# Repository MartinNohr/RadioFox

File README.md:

# RadioFox
Ham Radio Fox Software
This is the code for a TTGO T-Display running an SA818V radio. It is used for fox/bunny hunting.
This code requires the phoneDTMF library from here:
https://github.com/Adrianotiger/phoneDTMF
Install as documents/arduino/libraries/phoneDTMF

7/1/2026 The code has been changed to use VS Code with the pio extension loaded. Load the dtmf file into the VS Code lib folder.
The code also now uses espressif version 3.x instead of 2.x. They had introduced a number of breaking changes in version 3.x that resulted in numerous code changes.

7/28/2026 I went back to core 2.0.17. The 3.x one rebooted constantly. I'll spend some time later figureing out why.

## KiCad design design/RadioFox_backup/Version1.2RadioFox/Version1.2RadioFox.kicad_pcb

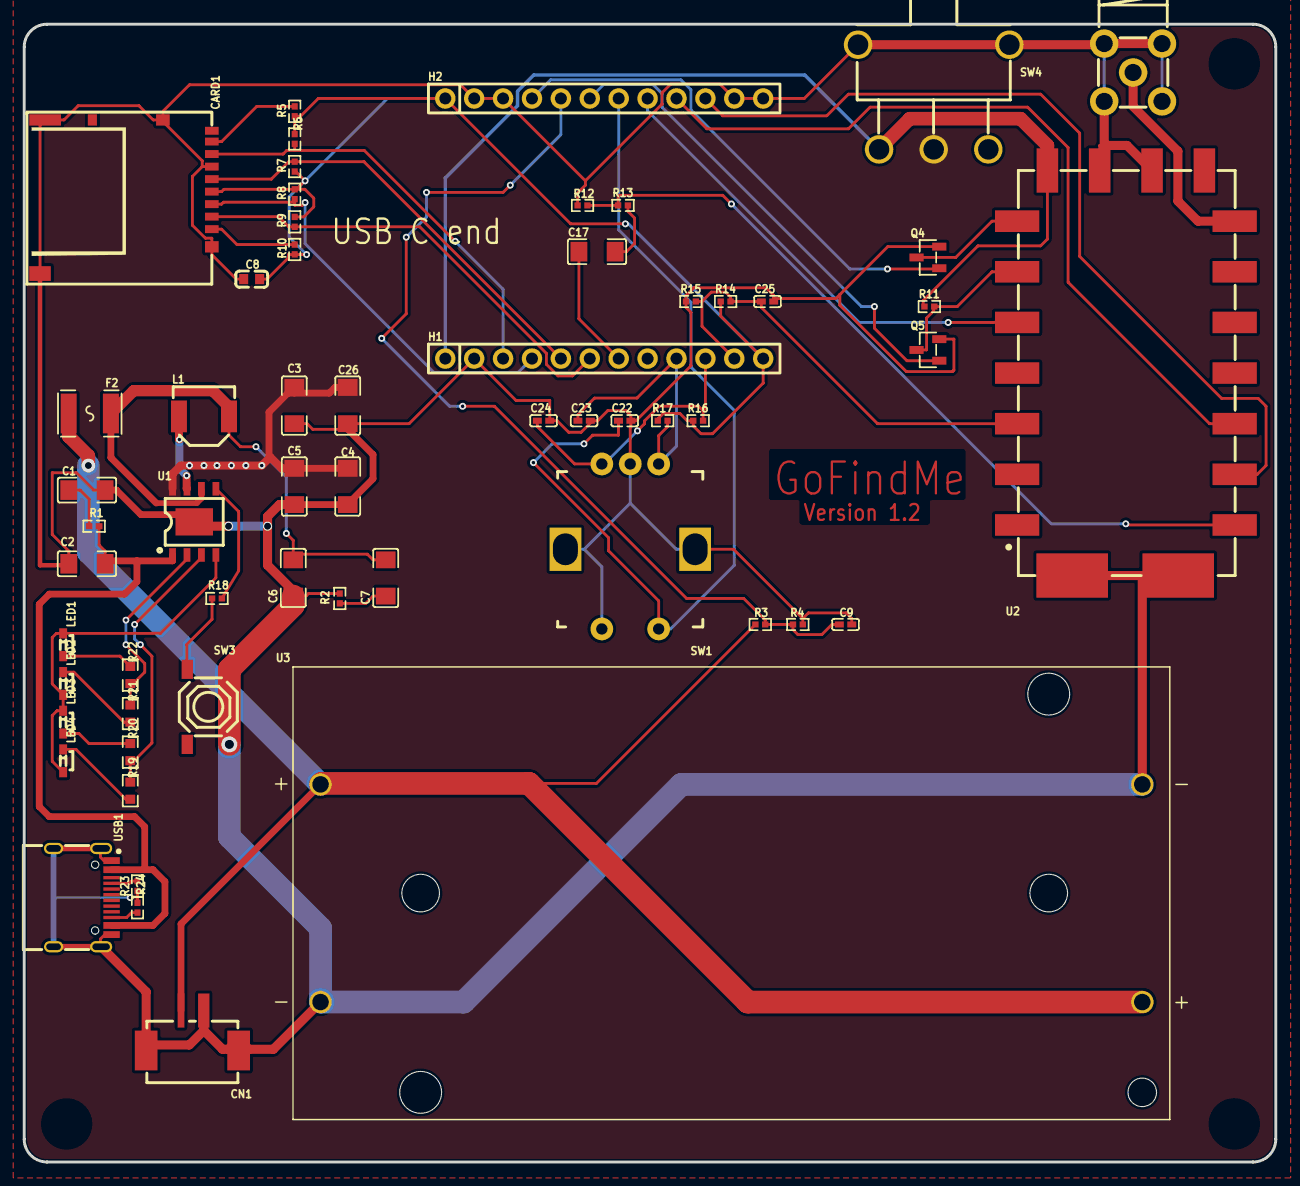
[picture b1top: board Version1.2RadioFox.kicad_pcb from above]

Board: 2 copper layers, 110.0 x 100.0 mm, 59 parts (0 on the bottom side), 43 nets.

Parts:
C1, C2, C3, C4, C5, C6, C7, C17, C26: C1206
C8: C0603
C9, C22, C23, C24, C25: C0402
CARD1: SD-SMD_DM3AT-SF-PEJM5
CN1: conn-smd_ph2.0-1x2pw
F2: F1812
H1, H2: HDR-TH_12P-P2.54-V-F
L1: IND-SMD_L5.4-W5.1_SPM5020
LED1, LED2, LED3, LED4: LED-SMD_L2.0-W1.1-R-RD-SIDE_WHITE
Q4, Q5: SOT-23-3_L2.9-W1.3-P1.90-LS2.4-BR
R1: r0402
R2, R3, R4, R5, R6, R7, R8, R9, R10, R11, R12, R13, R14, R15, R16, R17, R18, R23, R24: R0402
R19, R20, R21, R22: R0603
RF1: SMA-TH_KH-SMA-P-8496
SW1: sw-th_pec11r-4220f-s0012
SW3: SW-SMD_4P-L5.1-W5.1-P3.70-LS6.5-TL-2
SW4: SW-TH_SS-12D11L5
U1: ESOP-8_L4.9-W3.9-P1.27-LS6.0-BL-EP
U2: WIRELM-SMD_G-NICERF_SA818S-X
U3: BAT_1049P
USB1: USB-SMD_YTC-TC16-473

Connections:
3V3: C8.1, CARD1.4, H1.12, H2.1, R5.1, R6.1, R7.1, R8.1, R9.1, R10.1, R14.1, R16.1, R17.1
5V: H1.1, R11.1, SW4.1, U2.8
5VREG: C3.1, C4.1, C5.1, C26.1, SW4.2, U1.8
$2N118: CARD1.7, H1.3, R6.2
$2N119: CARD1.3, H1.4, R8.2
$2N120: CARD1.5, H1.5, R7.2
$2N121: CARD1.8, R5.2
$2N122: CARD1.2, H1.6, R9.2
$2N123: CARD1.1, R10.2
$2N921: C1.2, R1.1
$2N930: R12.1, R13.1, U2.18
$2N934: C17.2, R13.2
$2N9497: C7.1, R2.1
$2N10454: L1.1, U1.7
$2N10458: C6.2, C7.2, F2.1, L1.2, U1.6
$2N33469: R18.1, SW3.2
$2N33473: R18.2, U1.5
$2N85905: LED1.1, R22.1
$2N85915: LED2.2, R21.1
$2N85988: LED3.1, R20.1
$2N85990: LED4.2, R19.1
$2N93035: R24.2, USB1.B5
$2N93039: R23.2, USB1.A5
AF_OUT: C25.1, H1.11, R14.2, R15.2, U2.3
ANT: RF1.5, U2.12
BATLEVELSENSE: C9.2, H2.5, R3.2, R4.1
GND: C1.1, C2.1, C3.2, C4.2, C5.2, C6.1, C8.2, C9.1, C22.2, C23.2, C24.2, C25.2, C26.2, CARD1.6, CARD1.10, CARD1.12, CARD1.13, CARD1.14, CN1.1, CN1.3, CN1.4, H1.2, H2.2, H2.3, H2.11, H2.12, Q4.2, Q5.2, R2.2, R4.2, R12.2, R15.1, R23.1, R24.1, RF1.1, RF1.2, RF1.3, RF1.4, SW1.2, SW1.3, SW1.C, SW3.3, SW3.4, SW4.4, SW4.5, U1.9, U2.9, U2.10, U2.19, U2.20, U3.2, U3.3, USB1.1, USB1.2, USB1.3, USB1.4, USB1.A1B12, USB1.B1A12
H/L: Q4.3, U2.7
H/L_SIG: H2.4, Q4.1
LED1: R21.2, R22.2, U1.2
LED2: R19.2, R20.2, U1.3
LED3: LED1.2, LED2.1, LED3.2, LED4.1, U1.4
MIC-INPUT: C17.1, H1.7
POWER: C2.2, R1.2, U1.1, USB1.A4B9, USB1.B4A9
PTT: H2.8, U2.5
RADIO_SLEEP: Q5.3, R11.2, U2.6
RX_RF: H2.9, U2.16
SLEEP_CONTROL: H2.6, Q5.1
SW1: C22.1, H2.7, SW1.1
SWA: C23.1, H1.9, R17.2, SW1.A
SWB: C24.1, H1.10, R16.2, SW1.B
TX_RF: H2.10, U2.17
VBAT+: CN1.2, F2.2, R3.1, U3.1, U3.4

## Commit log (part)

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2023-03-27 Add .gitattributes and .gitignore.
2023-03-27 Add project files.
2023-04-02 Added fonts.h.
2023-06-29 Getting closer to compiling
2023-07-09 Fixed includes and some more code.
2023-07-10 More code cleanup.
2023-07-10 Compiles and links, but not really working yet.
2023-07-11 Fixed bugs.
2023-07-11 Menu changes.
2023-07-11 Main screen changes.
2023-07-12 Fixed radio frequencty range and added edit radio call ID.
2023-07-15 Fixed config saving/loading and menu changes.
2023-07-16 Select audio file coded, but not quite complete, scrolling not finished yet.
2023-07-16 Fixed audio file selection to hilite the current selection.
2023-07-17 Removed the unused LED timer.
2023-07-17 Added PTT control to transmit.
2023-07-17 Keep the TX timer running even when in menus. Menus will delay the transmit though until exited.
2023-07-17 Fixed missing init of LCD display dim timer. Removed display main screen code, it is now a task so not needed.
2023-11-24 Fixed crash problem and made task stacks 4000, a more reasonable size. The crash is caused by tasks writing to the TFT which is not re-entrant. Need to add some mutexes to really fix. For now just tu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
2023-11-24 Added mutex with LockDisplay and UnLockDisplay to control display access.
2023-11-24 Lock the screen when menus are opened, and unlock when closed.
2023-11-25 Added the call to sendmusic. Changed the tone generator to channel 2.
2023-11-25 Added SendBeacon() call.
2023-11-27 Many changes with tasks doing all the work now. Fixed the battery display to only run every 60 seconds, it takes a long time and messes up the run display.
2023-11-27 Attempt to fix display of battery after menus, not working but don't want to lose this code.
2023-11-27 Fixed updating the battery level after showing the menus.
2023-11-27 Fixed a problem when trying immediate stop during music, the flag was ignored in the Beacon part so it didn't stop there.
2023-11-28 Fixed a crash caused when changing settings and the eeprom save code wrote to the unlocked display at the same time as the run radio task.
2023-11-29 Switched serial output to 12, pin 22 seems to follow the morse out, don't know why yet.
2023-11-29 Stop all sending tasks after timeot, there was often one left running.
2023-11-29 Turn off audio out after all sending operations are stopped.
2023-11-30 Created an array and loop to run the music and beacon tasks. This will make it easier to add more similar ones without duplicating code in the future.
2023-12-02 Fixed sideways scrolling on menus and displays.
2023-12-03 Moved scrolling and menu handling to tasks. Fixed the integer edit screen to fix the blinking of the bar, it was redrawing constantly.
2023-12-03 Added RX offset for 0 +-600 kHz.
2023-12-04 Removed the bHue argument from the integer helper function, it wasn't used.
2023-12-05 Added 1200 kHz for offset with UHF.
2023-12-08 Added the serial number to the system display. It can't be edited. Should that be allowed?
2023-12-08 Added some preliminary radio setup code. Still working on it.
2023-12-09 Frequency needed to be divided by 1000.0 not multiplied, to send to the radio.
2023-12-09 The correct format for the frequency should be %.4f.
2023-12-09 Enabled HiPower control. When you use pinMode you have to use DigitalWrite and when you use gpio... you need to use gpio... to control outputs.
2023-12-16 Fixed some more sideways scrolling issues, sometimes a scrolled line would be duplicated until the menu was redrawn.
2023-12-16 Changed main screen "Cycles" to "TX Count".
2023-12-26 Talking to the radio now but sometimes crashes and reboots when changing settings.
2023-12-26 Bumped the menu task priority up to improve responsiveness.
2023-12-26 Changed back to "pause" in send menu. Created defines for PTT talk and listen.
2023-12-26 Setup the radio when any system setting is changed, makes code easier to maintain and doesn't really hurt anything. Added menu items to select CTSS frequencies.
2023-12-27 Fixed some crashing when entering beacon and id strings. Caused by not delaying to allow the watchdog to be called. There was also a chance that the id strings might be changed while being sent, if s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
2023-12-27 Fixed DTMF handler, the begin needed to filter higher frequencies, set to limit at 2kHz, which will pass all DTMF. The handling code needs some improvements, but it does work now.
2023-12-28 Added the Easyedapro file in the design folder. This is also where the 3D enclosure plans will be.
2023-12-29 Changed the main screen to always show the radio settings.
2023-12-29 Updated schematic.
2023-12-29 Changed DTMF to use '4' to turn off instead of anything else.
2023-12-30 Fixed wiring error in the schematic.
2023-12-31 Improved layout for better routing.
2024-01-01 Started routing some of lines manually.
2024-01-01 Fixed battery reverse protection, I think.
2024-01-02 Correct main display, high and low power were reversed.
2024-01-03 Move H/L radio control to GPIO12, and used GPIO15 for radio sleep control. Pin 12 must be allowed to float low or the esp32 won't boot.
2024-01-03 Added FET to control sleep, is isn't safe to pullup 5V on esp32 inputs according to the esp32 forum.
2024-01-04 Update README.md
    Added DTMF library location.
2024-01-04 DTMF now needs '*' to activate following commands. There is also a timer set how long commands will be accepted after '*'. This time gets set after each valid command so multiple commands can be sent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
2024-01-04 Removed debug message and changed delay limit from 0 to 120 minutes. Also tried to stop the transmission when the radio needs to be initialized, doesn't work reliably, but probably not a big deal.
2024-01-05 Fixed the issue stopping sending while waiting for radio to be initialized.
2024-01-05 Cleaned up some redundant clearscreen calls.
2024-01-05 The main screen status messages weren't always correct when a delay was set. Fixed now. Disabled wifi menu until available.
2024-01-05 Btn0 toggles the run state, it does not save the new state, the menu entry must still be used for that, but it does provide a quick way to start/stop. Only initialize the radio when one of the settin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
2024-01-06 Updated battery holder on schematic
2024-01-07 Added battery connector to PCB.
2024-01-07 Added DCS squelch unlocking codes. Fixed a bug with setting CTCSS codes, the format was wrong to the radio, needed to always be 4 characters, like "0000".
2024-01-07 Improved the DTMF code. Seems to be working now.
2024-01-08 The radio menu got too long. Rearranged things.
2024-01-08 Changed display timer dim value to go from 0 to 100 instead of 1 to 100. DIsplay might as well be completely off to save a little more power.
2024-01-09 Updated and fixed schematic. The H/L signal was accidentally shorted to ground.
2024-01-11 Improved new PCB layout.
2024-01-13 Circuit board improvements, including radio daughterboard.
2024-01-14 Schematic cleanup.
2024-01-14 Updated radio daughterboard.
2024-01-15 Layout changes.
2024-01-15 Moved power supply away from radio chip.
2024-01-15 Initial Route, needs cleanup.
2024-01-16 Shorten the DTMF delay when the timer is active so only the first '*' takes longer. Added system menu entry to check the 5V value. Put dial button debounce back to 20mS. The noise problem was caused 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
2024-01-17 Updated bin file.
2024-01-17 Fix a capacitor pad size.
2024-01-19 Updated to latest board and tft libraries.
2024-01-20 Changes in case of TTGO S3 future.
2024-01-22 BTN0Long will now cancel the current state and go the next one. e.g. if was transmitting it will go to pause, and if was pause will go to transmitting.
2024-02-18 Includes the WavPlayer code using PDM, experimental.
2024-02-20 Minor I2S changes.
2024-02-21 Added option to play or not to play the Tetris theme. #11
2024-04-05 Empty the radio rx buffer before sending. This was needed on the PCB version since the radio sends 15 nulls after power up. The String() library ReadString will store nulls and they cause indexOf to 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
2024-04-05 Flush the radio buffer before sending commands to it. The radio was sometimes not initializing after power up.
2024-04-06 Added an auto retry for a couple of times in case the radio didn't get the message during setup.
2024-04-06 Set better voltage values and removed the USB voltage display which only works on the TTGO USB port.
2024-04-10 Added a simple animation to the bottom left of the display during transmitting.
2024-04-16 Added radio sleep during pause. This will of course disable DTMF, but should save some power. Increased the sideways scrolling priority so it was smoother. Changed battery display task to 10 seconds.
2024-04-17 Set battery back to 15 seconds pause. Put more accurate values in default battery full and empty values.
2024-04-26 Fixed bezel position and improved the top mounting
    Also added screw holes for the PCB.
2024-04-26 fixed the bezel chimney
2024-04-27 improved retaining lip
2024-04-27 added cooling vents
2024-04-30 adjusted bezel for TTGO variations
2024-05-01 Fixed a problem with some radios not sending. Moved the RadioSerial setup later in the code. I think the radios don't boot up correctly sometimes if the RXD line is raised too fast. Anyway, this fixe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
2024-05-02 Added automatic battery full calibration. Initialize the battery smoother so it starts reading faster.
2024-05-02 Removed the automatic battery calibration, didn't work well. Added manual battery calibration so it can match the IP5306 chip.
2024-05-03 Limit transmit to 90 seconds, the radio gets really hot!
2024-05-04 Music line on main display duplicated.
2024-05-04 Added an option for fixed or random timers for xmit and pause.
2024-05-06 Added settings files. Current settings can be saved into named files that can be loaded anytime.
2024-05-09 Fixed CTCSS so it doesn't get set to index -1 when dial is clicked, which should have ignore any changes.
2024-05-10 Added separate menu item to create a settings file. Changed the file save to save/update. Sorted the settings file list. Removed the kludgy global for choosing settings files.
2024-05-11 Added setting for hilite color.
2024-05-11 Added indicators to which color is being changed. Changed version to 1.00. Fixed display of hilite colors.
2024-05-11 Fixed run screen to use menutextcolor on all lines.
2024-05-12 Added battery support to case top and a slot to see the charge leds.
2024-05-13 Updated docx file.
2024-05-14 Added the correct BIN file for this hardware.
2024-05-14 Slightly thinner top battery stop
2024-05-14 Made TX red dot larger. Show DTMF characters in green on the bottom. (not tested yet)
2024-05-16 Change prompts BTN0/1 to B0/1. That matches the label on the box.
2024-05-17 Fixed the hang problem. #26
2024-05-17 Added the bin file.
2024-05-22 hole size improvements
2024-05-22 improved sd and usb hole sizes
2024-06-11 Added beacon mode to restrict frequency range. #29
2024-08-07 Change "Beacon Frequency Mode" in menus to "Beacon Frequency". Added DTMF documentation to docx file.
2024-08-21 Show total on time on main screen.
2024-08-24 Updated 3D files.
2024-08-25 Updated DOCX file with the USB-C cable issue.
2024-08-28 Added bin file
2024-11-05 Added floats to menu system. Used for latitude and longitude settings.
2024-11-05 Fixed GPS floating point entry. Changed Beacon to Radio ID to avoid confusion with beacon mode.
2024-11-05 Current bin file.
2024-11-05 New bin file.
2024-11-05 GPS task wasn't killing itself when done. Changed some of the text for clarity while sending.
2024-11-06 Fixed crash caused by not using mutex around the progress bar. Reverse float entry to start at least significant digit.
2024-11-07 Added boolean to control sending GPS or not only when beacon mode is on.
2024-12-01 Recompiled bin file.
2024-12-02 Moved B0/B1 text away from thin hinge area.
2024-12-02 More text improvements.
2024-12-29 Some beginning Kicad files and update docx file.
2025-09-19 DOCX changes describing batteries. Also the latest gerber files used for NextPCB.com.
2026-06-28 VS Code version of the code
2026-06-29 more updates
2026-06-30 Vs code version (#34)
    * VS Code version of the code
    * Changes to esp32 espressif release 3.x
    * Add files via upload
    * more updates
    * Add files via upload
    * Add files via upload
